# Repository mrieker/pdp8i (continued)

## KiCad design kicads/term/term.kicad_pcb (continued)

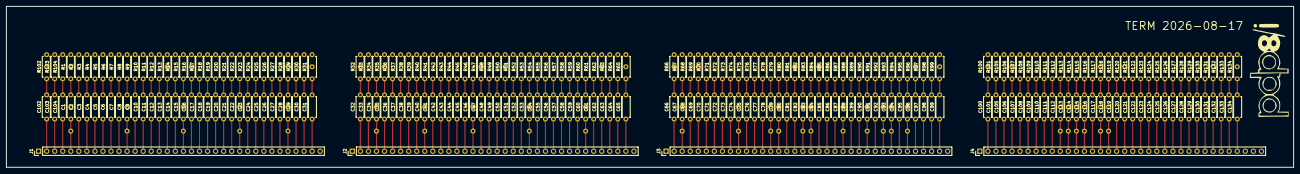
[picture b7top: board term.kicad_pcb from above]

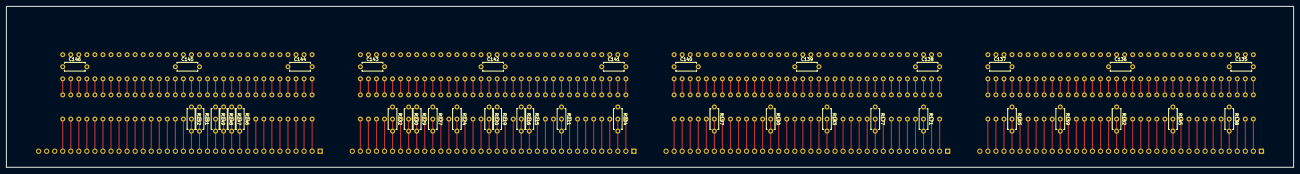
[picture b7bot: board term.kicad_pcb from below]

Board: 4 copper layers, 406.4 x 50.8 mm, 311 parts (39 on the bottom side), 270 nets.
